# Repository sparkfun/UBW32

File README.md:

USB 32-Bit Whacker-PIC32MX795 Development Board
================================================

[
*USB 32-Bit Whacker (DEV-09713)*](https://www.sparkfun.com/products/9713)

This breadboard friendly development board enables you to get the PIC32 up and running quickly. 
Power can be provided over USB, there are 3 push buttons (including 2 user-defined buttons),
and 5 indicator LEDs. The board comes pre-loaded with a USB bootloader and special UBW firmware that accepts
simple serial commands to control the various I/O functions. 

Repository Contents
-------------------
* **/Hardware** - All Eagle design files (.brd, .sch, .STL)

License Information
-------------------
Distributed as-is; no warranty is given.

This product is a collaboration with Brian Schmalz.

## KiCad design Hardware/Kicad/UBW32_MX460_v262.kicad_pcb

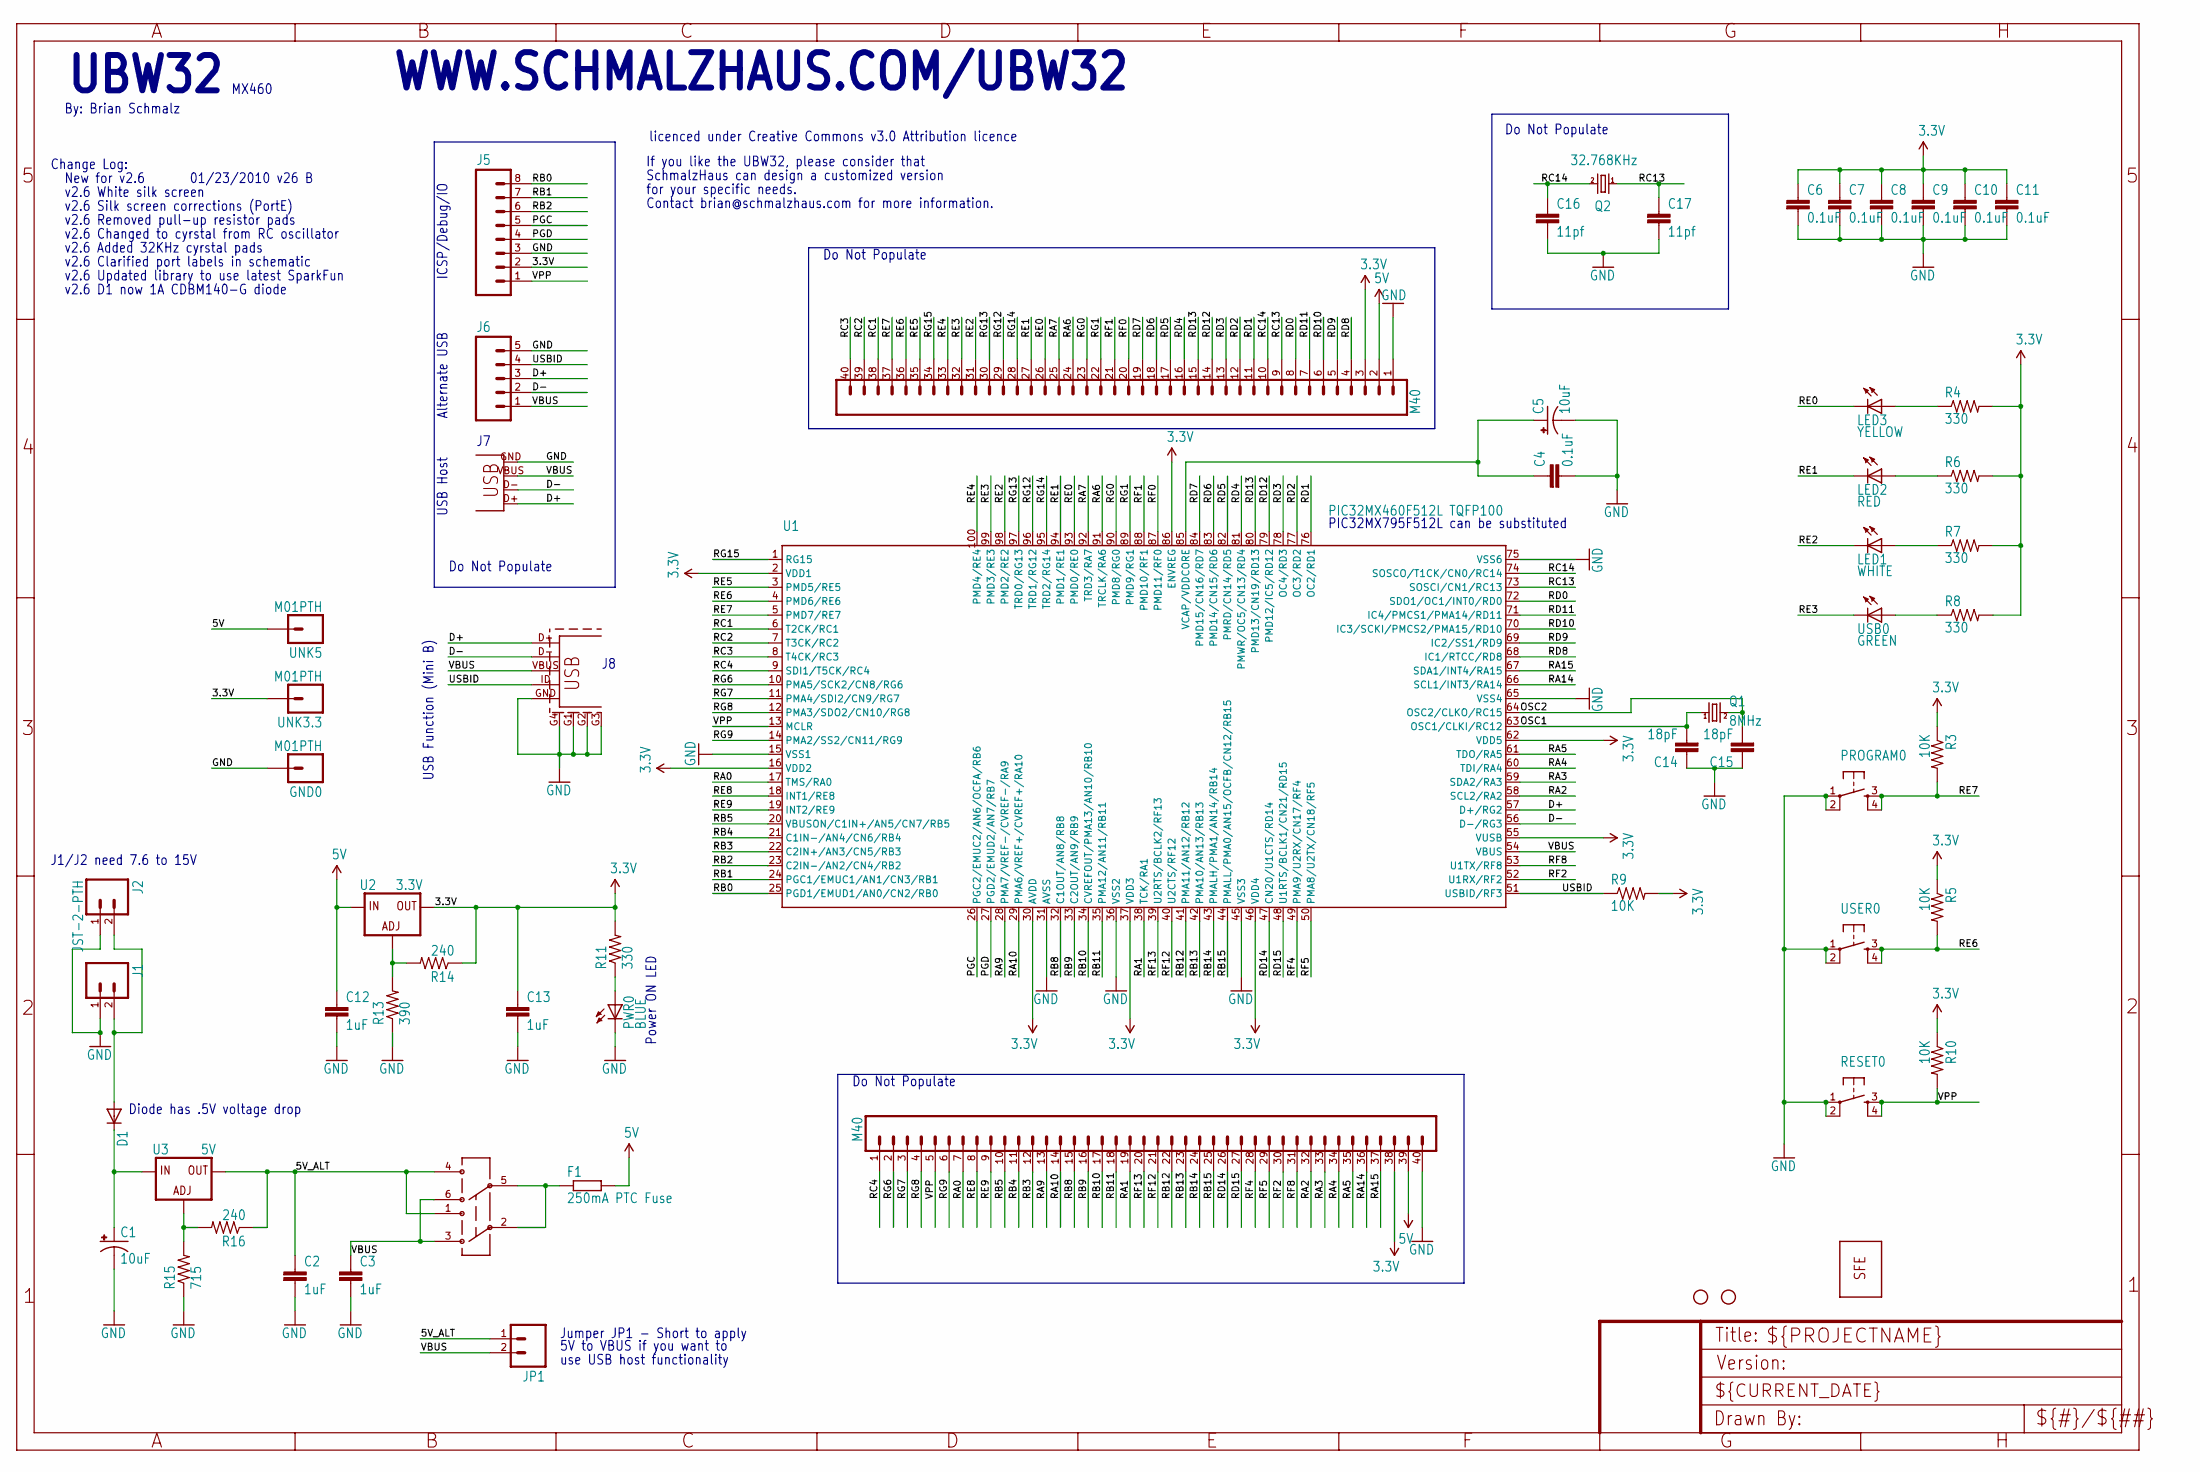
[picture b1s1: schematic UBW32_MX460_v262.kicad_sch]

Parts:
C1, C5: 10uF; EIA3528
C2, C3: 1uF; 0402-CAP
C4, C6, C7, C8, C9, C11: 0.1uF; 0402-CAP
C10: 0.1uF; C0402
C12, C13: 1uF; C0402
C14, C15: 18pF; 0402-CAP
C16, C17: 11pf; 0402-CAP
D1: DIODESMA; SMA-DIODE
F1: 250mA PTC Fuse; R1206
GND0: M01PTH; 1X01
J1: M02PTH; 1X02
J2: JST-2-PTH; S2B-PH
J3, J4: M40; 1X40
J5: M08; 1X08
J6: M05PTH; 1X05
J7: USB-A-S
J8: USB-MINIB
JP1: M02PTH; 1X02
LED1: WHITE; LED-0603
LED2: RED; LED-0603
LED3: YELLOW; LED-0603
PROGRAM0: TAC_SWITCHSND; TACTILE_SWITCH_SMD
PWR0: BLUE; LED-0603
PWR_SEL0: AYZ0202
Q1: 8MHz; CRYSTAL-SMD-5X3
Q2: 32.768KHz; CRYSTAL-32KHZ-SMD
R3, R5, R9, R10: 10K; 0402-RES
R4, R6, R7, R8, R11: 330; 0402-RES
R13: 390; 0402-RES
R14, R16: 240; 0402-RES
R15: 715; 0402-RES
RESET0: TAC_SWITCHSND; TACTILE_SWITCH_SMD
U1: PIC32MX460F512L TQFP100; TQFP100
U2: 3.3V; SOT223
U3: 5V; SOT223
U$4: LOGO-SFENEW; SFE-NEW-WEBLOGO
U$6, U$7: STAND-OFF
UNK3.3, UNK5: M01PTH; 1X01
USB0: GREEN; LED-0603
USER0: TAC_SWITCHSND; TACTILE_SWITCH_SMD

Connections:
3.3V: C6.1, C7.1, C8.1, C9.1, C10.1, C11.1, C13.1, J3.3, J4.38, J5.2, R3.1, R4.2, R5.1, R6.2, R7.2, R8.2, R9.2, R10.1, R11.2, R14.1, U1.2 (VDD1), U1.16 (VDD2), U1.30 (AVDD), U1.37 (VDD3), U1.46 (VDD4), U1.55 (VUSB), U1.62 (VDD5), U1.86 (ENVREG), U2.2 (OUT), UNK3.3.1
5V: C12.1, F1.2, J3.2, J4.39, U2.3 (IN), UNK5.1
5V_ALT: C2.1, JP1.1, PWR_SEL0.1 (3), PWR_SEL0.4 (6), R16.1, U3.2 (OUT)
D+: J6.3, J7.D+, J8.D+, U1.57 (D+/RG2)
D-: J6.2, J7.D-, J8.D-, U1.56 (D-/RG3)
GND: C1.C (-), C2.2, C3.2, C4.2, C5.C (-), C6.2, C7.2, C8.2, C9.2, C10.2, C11.2, C12.2, C13.2, C14.1, C15.1, C16.2, C17.2, GND0.1, J1.1, J2.1, J3.1, J4.40, J5.3, J6.5, J7.GND, J8.G1, J8.G2, J8.G3, J8.G4 (SHIELD), J8.GND, PROGRAM0.1, PROGRAM0.2, PWR0.C, R13.1, R15.1, RESET0.1, RESET0.2, U1.15 (VSS1), U1.31 (AVSS), U1.36 (VSS2), U1.45 (VSS3), U1.65 (VSS4), U1.75 (VSS6), USER0.1, USER0.2
unnamed: D1.A, J1.2, J2.2
unnamed: F1.1, PWR_SEL0.2, PWR_SEL0.5
unnamed: R13.2, R14.2, U2.1 (ADJ)
unnamed: R15.2, R16.2, U3.1 (ADJ)
unnamed: PWR0.A, R11.1
unnamed: R8.1, USB0.A
unnamed: LED1.A, R7.1
unnamed: LED2.A, R6.1
unnamed: LED3.A, R4.1
unnamed: C4.1, C5.A (+), U1.85 (VCAP/VDDCORE)
OSC1: C14.2, Q1.1, U1.63 (OSC1/CLKI/RC12)
OSC2: C15.2, Q1.3 (2), U1.64 (OSC2/CLKO/RC15)
PGC: J5.5, U1.26 (PGC2/EMUC2/AN6/OCFA/RB6)
PGD: J5.4, U1.27 (PGD2/EMUD2/AN7/RB7)
RA0: J4.7, U1.17 (TMS/RA0)
RA1: J4.19, U1.38 (TCK/RA1)
RA2: J4.32, U1.58 (SCL2/RA2)
RA3: J4.33, U1.59 (SDA2/RA3)
RA4: J4.34, U1.60 (TDI/RA4)
RA5: J4.35, U1.61 (TDO/RA5)
RA6: J3.24, U1.91 (TRCLK/RA6)
RA7: J3.25, U1.92 (TRD3/RA7)
RA9: J4.13, U1.28 (PMA7/VREF-/CVREF-/RA9)
RA10: J4.14, U1.29 (PMA6/VREF+/CVREF+/RA10)
RA14: J4.36, U1.66 (SCL1/INT3/RA14)
RA15: J4.37, U1.67 (SDA1/INT4/RA15)
RB0: J5.8, U1.25 (PGD1/EMUD1/AN0/CN2/RB0)
RB1: J5.7, U1.24 (PGC1/EMUC1/AN1/CN3/RB1)
RB2: J5.6, U1.23 (C2IN-/AN2/CN4/RB2)
RB3: J4.12, U1.22 (C2IN+/AN3/CN5/RB3)
RB4: J4.11, U1.21 (C1IN-/AN4/CN6/RB4)
RB5: J4.10, U1.20 (VBUSON/C1IN+/AN5/CN7/RB5)
RB8: J4.15, U1.32 (C1OUT/AN8/RB8)
RB9: J4.16, U1.33 (C2OUT/AN9/RB9)
RB10: J4.17, U1.34 (CVREFOUT/PMA13/AN10/RB10)
RB11: J4.18, U1.35 (PMA12/AN11/RB11)
RB12: J4.22, U1.41 (PMA11/AN12/RB12)
RB13: J4.23, U1.42 (PMA10/AN13/RB13)
RB14: J4.24, U1.43 (PMALH/PMA1/AN14/RB14)
RB15: J4.25, U1.44 (PMALL/PMA0/AN15/OCFB/CN12/RB15)
RC1: J3.38, U1.6 (T2CK/RC1)
RC2: J3.39, U1.7 (T3CK/RC2)
RC3: J3.40, U1.8 (T4CK/RC3)
RC4: J4.1, U1.9 (SDI1/T5CK/RC4)
RC13: C17.1, J3.9, Q2.X1 (1), U1.73 (SOSCI/CN1/RC13)
RC14: C16.1, J3.10, Q2.X2 (2), U1.74 (SOSCO/T1CK/CN0/RC14)
RD0: J3.8, U1.72 (SDO1/OC1/INT0/RD0)
RD1: J3.11, U1.76 (OC2/RD1)
RD2: J3.12, U1.77 (OC3/RD2)
RD3: J3.13, U1.78 (OC4/RD3)
RD4: J3.16, U1.81 (PMWR/OC5/CN13/RD4)
RD5: J3.17, U1.82 (PMRD/CN14/RD5)
RD6: J3.18, U1.83 (PMD14/CN15/RD6)
RD7: J3.19, U1.84 (PMD15/CN16/RD7)
RD8: J3.4, U1.68 (IC1/RTCC/RD8)
RD9: J3.5, U1.69 (IC2/SS1/RD9)
RD10: J3.6, U1.70 (IC3/SCKI/PMCS2/PMA15/RD10)
RD11: J3.7, U1.71 (IC4/PMCS1/PMA14/RD11)
RD12: J3.14, U1.79 (PMD12/IC5/RD12)
RD13: J3.15, U1.80 (PMD13/CN19/RD13)
RD14: J4.26, U1.47 (CN20/U1CTS/RD14)
RD15: J4.27, U1.48 (U1RTS/BCLK1/CN21/RD15)
RE0: J3.26, LED3.C, U1.93 (PMD0/RE0)
RE1: J3.27, LED2.C, U1.94 (PMD1/RE1)
RE2: J3.31, LED1.C, U1.98 (PMD2/RE2)
RE3: J3.32, U1.99 (PMD3/RE3), USB0.C
RE4: J3.33, U1.100 (PMD4/RE4)
RE5: J3.35, U1.3 (PMD5/RE5)
RE6: J3.36, R5.2, U1.4 (PMD6/RE6), USER0.3, USER0.4
RE7: J3.37, PROGRAM0.3, PROGRAM0.4, R3.2, U1.5 (PMD7/RE7)
RE8: J4.8, U1.18 (INT1/RE8)
RE9: J4.9, U1.19 (INT2/RE9)
RF0: J3.20, U1.87 (PMD11/RF0)
RF1: J3.21, U1.88 (PMD10/RF1)
RF2: J4.30, U1.52 (U1RX/RF2)
RF4: J4.28, U1.49 (PMA9/U2RX/CN17/RF4)
RF5: J4.29, U1.50 (PMA8/U2TX/CN18/RF5)
RF8: J4.31, U1.53 (U1TX/RF8)
RF12: J4.21, U1.40 (U2CTS/RF12)
RF13: J4.20, U1.39 (U2RTS/BCLK2/RF13)
RG0: J3.23, U1.90 (PMD8/RG0)
RG1: J3.22, U1.89 (PMD9/RG1)
RG6: J4.2, U1.10 (PMA5/SCK2/CN8/RG6)
RG7: J4.3, U1.11 (PMA4/SDI2/CN9/RG7)
RG8: J4.4, U1.12 (PMA3/SDO2/CN10/RG8)
RG9: J4.6, U1.14 (PMA2/SS2/CN11/RG9)
RG12: J3.29, U1.96 (TRD1/RG12)
RG13: J3.30, U1.97 (TRD0/RG13)
RG14: J3.28, U1.95 (TRD2/RG14)
RG15: J3.34, U1.1 (RG15)
USBID: J6.4, J8.ID (USB_ID), R9.1, U1.51 (USBID/RF3)
VBUS: C3.1, J6.1, J7.VBUS, J8.VBUS, JP1.2, PWR_SEL0.3 (1), PWR_SEL0.6 (4), U1.54 (VBUS)
VIN_RAW: C1.A (+), D1.C, U3.3 (IN)
VPP: J4.5, J5.1, R10.2, RESET0.3, RESET0.4, U1.13 (MCLR)

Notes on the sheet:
PIC32MX795F512L can be substituted
5V to VBUS if you want to
SchmalzHaus can design a customized version
licenced under Creative Commons v3.0 Attribution licence
Do Not Populate
v2.6 D1 now 1A CDBM140-G diode
MX460
If you like the UBW32, please consider that
01/23/2010 v26 B
v2.6 Silk screen corrections (PortE)
v2.6 White silk screen
use USB host functionality
Change Log:
UBW32
Contact brian@schmalzhaus.com for more information.
v2.6 Updated library to use latest SparkFun
By: Brian Schmalz
USB Host
ICSP/Debug/IO
New for v2.6
v2.6 Added 32KHz cyrstal pads
v2.6 Removed pull-up resistor pads
Power ON LED
for your specific needs.
Jumper JP1 - Short to apply
v2.6 Clarified port labels in schematic
v2.6 Changed to cyrstal from RC oscillator
WWW.SCHMALZHAUS.COM/UBW32
J1/J2 need 7.6 to 15V
USB Function (Mini B)
Diode has .5V voltage drop
Alternate USB

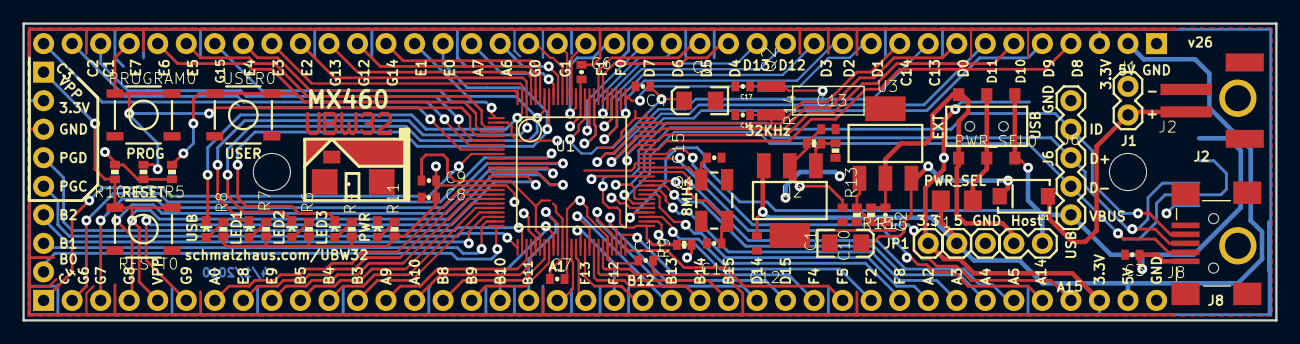
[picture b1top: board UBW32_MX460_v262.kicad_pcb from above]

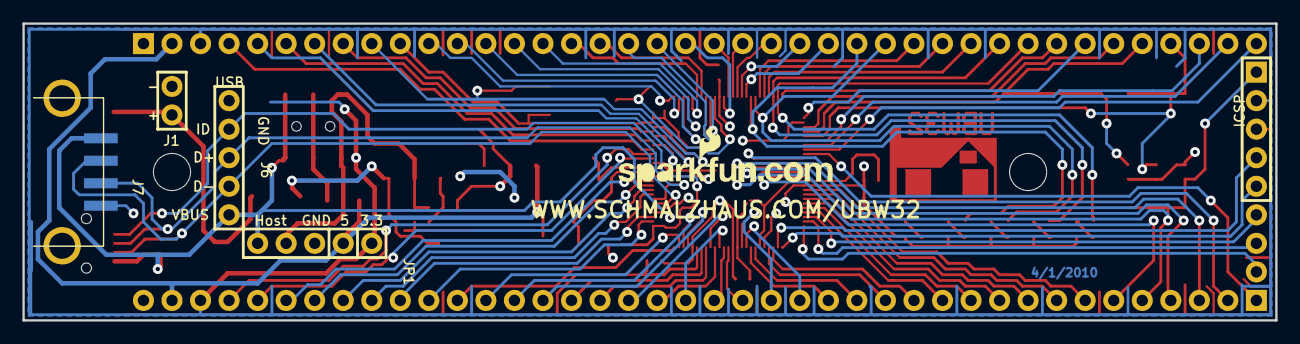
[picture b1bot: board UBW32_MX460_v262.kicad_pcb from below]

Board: 2 copper layers, 111.5 x 26.4 mm, 63 parts (2 on the bottom side), 100 nets.

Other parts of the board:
U$3: UBW32
U$5: SCHMALZHAUS

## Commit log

2014-08-19 Adding hardware files and README info
2015-09-29 new larger panel
2017-01-10 .brd file Values Updated
2017-01-11 .brd Values Added
